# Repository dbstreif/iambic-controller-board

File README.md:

# Iambic Controller Custom Hardware
### (Morse Code Keyer Hardware Interface)

A board design using ATtiny85 microcontroller that interfaces with an iambic CW keyer over TRS to USB.
This project provides hardware for the firmware project found here: [Iambic-Controller](https://github.com/dbstreif/iambic-controller)

To build and install on your microcontroller, please use the Arduino IDE with the Digistump additional boards manager:
[Digistump Additional Boards Manager](https://raw.githubusercontent.com/digistump/arduino-boards-index/master/package_digistump_index.json)

### Compatibility
Plug and play with VBand, MorseIT (IOS/Android), MorseKeyer Software (PC), and many other applications.

[Video of Device in Action](https://drive.google.com/file/d/1ocy6Hf0ZipwWTclOcQ86UAAeljgz8sle/view?usp=sharing)

Shield: [![CC BY 4.0][cc-by-shield]][cc-by]

This work is licensed under a
[Creative Commons Attribution 4.0 International License][cc-by].

[![CC BY 4.0][cc-by-image]][cc-by]

[cc-by]: http://creativecommons.org/licenses/by/4.0/
[cc-by-image]: https://i.creativecommons.org/l/by/4.0/88x31.png
[cc-by-shield]: https://img.shields.io/badge/License-CC%20BY%204.0-lightgrey.svg

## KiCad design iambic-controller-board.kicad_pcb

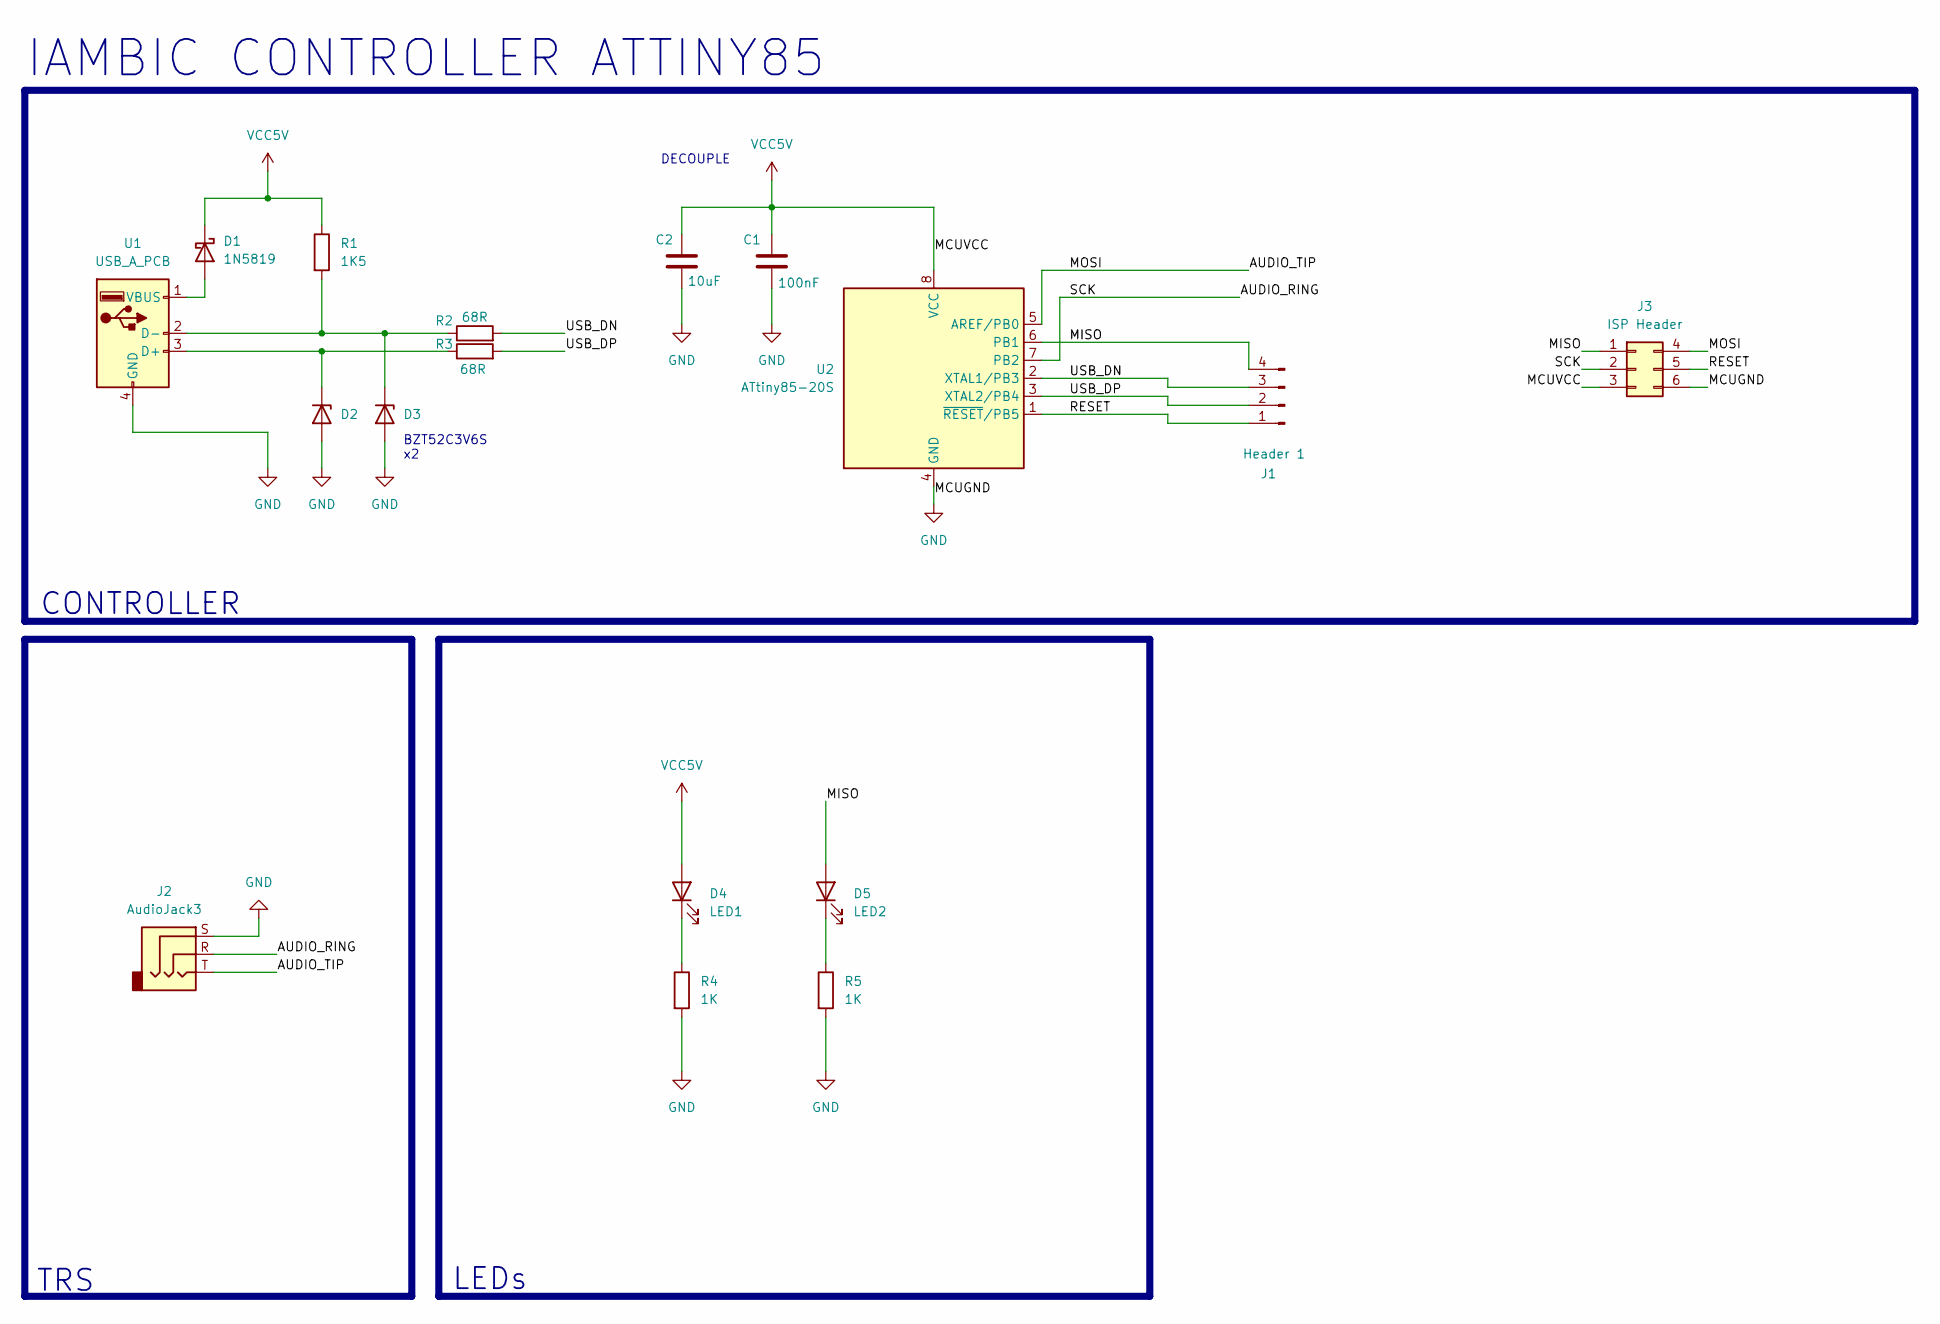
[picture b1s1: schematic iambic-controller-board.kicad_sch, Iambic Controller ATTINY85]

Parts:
C1: 100nF; C_0603_1608Metric
C2: 10uF; C_0603_1608Metric
D1: 1N5819; D_SOD-123
D2, D3: 3V6; D_SOD-323
D4: LED1; LED_0603_1608Metric
D5: LED2; LED_0603_1608Metric
J1: Header 1; PinHeader_1x04_P2.54mm_Vertical
J2: AudioJack3; Jack_3.5mm_CUI_SJ1-3515N_Horizontal
J3: ISP Header; Tag-Connect_TC2030-IDC-NL_2x03_P1.27mm_Vertical
R1: 1K5; R_0603_1608Metric
R2, R3: 68R; R_0603_1608Metric
R4, R5: 1K; R_0603_1608Metric
U1: USB_A_PCB; PCB_USB_A
U2: ATtiny85-20S; SOIC-8_5.3x5.3mm_P1.27mm

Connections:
/AUDIO_RING: J2.R, J3.2, U2.7 (PB2)
/AUDIO_TIP: J2.T, J3.4, U2.5 (AREF/PB0)
/MISO: D5.2 (A), J1.4, J3.1, U2.6 (PB1)
/RESET: J1.1, J3.5, U2.1 (~RESET/PB5)
/USB_DN: J1.3, R2.2, U2.2 (XTAL1/PB3)
/USB_DP: J1.2, R3.2, U2.3 (XTAL2/PB4)
GND: C1.1, C2.2, D2.2 (A), D3.2 (A), J2.S, J3.6, R4.2, R5.2, U1.4 (GND), U2.4 (GND)
unnamed: D1.2 (A), U1.1 (VBUS)
unnamed: D2.1 (K), R3.1, U1.3 (D+)
unnamed: D3.1 (K), R1.2, R2.1, U1.2 (D-)
unnamed: D4.1 (K), R4.1
unnamed: D5.1 (K), R5.1
VCC5V: C1.2, C2.1, D1.1 (K), D4.2 (A), J3.3, R1.1, U2.8 (VCC)

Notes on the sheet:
TRS
BZT52C3V6S x2
IAMBIC CONTROLLER ATTINY85
LEDs
DECOUPLE
CONTROLLER

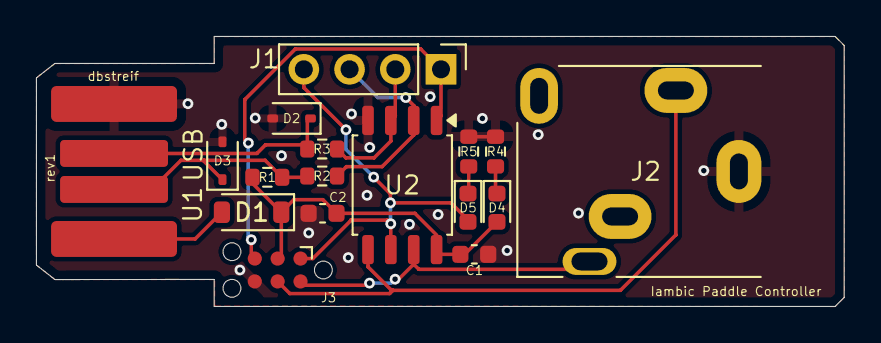
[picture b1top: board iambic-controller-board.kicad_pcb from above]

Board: 2 copper layers, 44.9 x 15.0 mm, 17 parts (0 on the bottom side), 13 nets.

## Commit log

2025-12-15 inited repo
2025-12-15 final rev1
2025-12-15 Remove drill and gerber files from repo
2025-12-15 Initialize README with project details and license
    Added detailed project description, compatibility information, and licensing.
2025-12-15 Fix formatting in README.md
    Removed extra line breaks in the README file.
2025-12-15 Added pictures
2025-12-15 Replace old image with new links in README
    Updated image links in the README file.
2025-12-15 Add Creative Commons license
    Added the Creative Commons Attribution-NonCommercial 4.0 International Public License to the project.
2025-12-15 Update README to clarify hardware interface
2025-12-16 Fixed weird footprints
2025-12-17 fixed route
2025-12-17 Updated pics
2026-03-30 Add video link to README
    Added a video link to the README for additional context.
2026-03-30 Update video link description in README
2026-03-30 Update video link to use preview format
2026-03-30 Embed video in README using iframe
    Replaced video link with an iframe for better embedding.
2026-03-30 Update README to link video instead of embedding
    Removed HTML video embed and replaced with a link.
2026-03-30 Update description of PCB design in README
